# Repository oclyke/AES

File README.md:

# AES

This repo contains folders for both hardware and software. 

Hardware is designed in Eagle.

Software uses the HAL library for STM32F4 and I reccomend the Atollic TRUEStudio development environment. STM32Cube is a great tool for generating skeleton code and configuring peripherals.

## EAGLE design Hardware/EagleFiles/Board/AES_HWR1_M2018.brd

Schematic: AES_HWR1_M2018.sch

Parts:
C1, C7, C18, C25, C26, C27, C29, C30, C32, C36, C38, C39, C40, C41, C42, C43, C44: 0.1uF; 0603
C2, C19: 10uF; 1206
C3, C10, C11, C12, C13: 560pF; 0603
C4: 220uF; 2917_P
C5: 22uF; 1206
C6, C8, C14, C15, C20, C28, C31, C33, C45: 1uF; 0603
C16: 150pF; 0603
C17: 4.7uF, 25V; 0603
C21, C22: 30pF; 0603
C23, C24: 10uF; 0603
C34, C35: 10pF; 0603
C37: 4.7uF; 0603
D1: 18V, 5W; DO-214AA
D2: 3V3; 0603-POLAR
D3, D7: PASS_DIODE_SCHOTTKY-LSM115J; DO-214BA
D4: OBD_STAT; 0603-POLAR
D5: OBD_ACT; 0603-POLAR
D6: OBD_HOST_ACT; 0603-POLAR
D8, D9: PASS_DIODE_ESD_CAN-PESD1CAN-UX; SOT23-3
D10, D11, D12, D13, D20, D21: PASS_DIODE_GEN-1N4148X; SOD-523
D14: BLU_CONN; 0603-POLAR
D15: TXRX_ACT; 0603-POLAR
D16: 5V; 0603-POLAR
D18: UL1; 0603-POLAR
D19: UL2; 0603-POLAR
F2: PASS_FUSE_POLY-1206L200SLYR; 1206
F3: 500mA; 1206
J1: BFR; 1X02
J2: BSB; 1X02
J3: BSM; 1X02
J4: BAD; 1X02
J5: BOOT1; 1X03
J6: SWD; 1X04
J7: RESET_NVM_L; SMD_HEADER_0.1IN_2POS
J8: BOOT0; 1X02
M1: SD CARD; SD_AMPHENOL_PUSH_PULL
M2: USB_MICRO-MID_MOUNT_REVERSIBLE; MICROUSB
M3: ALED0; 3_PIN_LOCK
M4: ALED1; 3_PIN_LOCK
M5: ALED2; 3_PIN_LOCK
M6: ALED3; 3_PIN_LOCK
M7: I2C_EXP; 4_PIN_LOCK
M8: UART EXP; 4_PIN_LOCK
M9: AUX PWR; 2_PIN_LOCK
M10: OBD_CONN-4-794627-6; OBD_16_SMD
M11: SIG_IN; 4_PIN_LOCK
M12: EXT_PWR_SW; 3_PIN_LOCK
Q1, Q2, Q3, Q4, Q9, Q10, Q11: PASS_NMOS-2N7002K; SOT23-3@1
Q5, Q7, Q12, Q17: AMP_MOSFET_PCH-MCQ4459; SOP-8
Q6, Q15, Q16, Q18, Q19, Q20, Q21, Q22, Q23, Q24, Q25, Q26, Q27: AMP_MOSFET_NCH-2N7002K; SOT23-3
Q8: PASS_PMOS-MCQ4459; SOP-8@1
Q13, Q14: AMP_BJT_NPNZXTN19100CFF; SOT23-3
R1, R2, R3, R4, R5, R6, R7, R8, R11, R13, R19, R37, R38, R39, R40, R44, R45, R46, R47, R49, R50, R51, R52, R53, R54, R55, R66, R67, R70, R71, R72, R73, R74, R75, R76, R77, R78, R79, R80, R81, R82, R83, R84, R85, R86, R87, R88, R89, R90, R91, R94, R101, R102, R104: 10k; 0603
R9: TRMD; 0603
R10: TRMU; 0603
R12, R92: 22; 0603
R14, R105: 300; 0603
R15, R16: PASS_RES-SMD_0603; 0603
R17: 10; 0603
R18: 62k; 0603
R20, R21, R22, R68, R69, R95, R96: 330; 0603
R23, R24, R59, R60, R61, R62, R63, R64: 100k; 0603
R25, R26, R99, R100: 4k7; 0603
R27, R28, R29, R30: 100; 0603
R31, R35, R36, R56, R58: 1k; 0603
R32: 6k49; 0603
R33, R34: 510 1/2W; 1206
R41: 240; 0603
R42: 866; 0603
R43: 374; 0603
R48: 2k7; 0603
R57, R65: 1k5; 0603
R93: 1M; 0603
R97, R98: 2k2; 0603
R103: 130 2W; 2512
S1: RESET; PTS525
S2: US2; PTS525
S3: US1; PTS525
S4: SWITCH_SPDT_SLIDE_SPARKFUN_SMD; SPARKFUNSWITCH
TP1: GPIO2; PAD.03X.05
TP2: REV3V3; PAD.03X.05
TP3: RTS3V3; PAD.03X.05
TP4: LTS3V3; PAD.03X.05
TP5: BRK3V3; PAD.03X.05
TP6: REV12V; PAD.03X.05
TP7: RTS12V; PAD.03X.05
TP8: LTS12V; PAD.03X.05
TP9: BRK12V; PAD.03X.05
TP10, TP71: VRAW; PAD.03X.05
TP11: VREVP; PAD.03X.05
TP12: VBATT; PAD.03X.05
TP13: 5V; PAD.03X.05
TP14: 3V3; PAD.03X.05
TP15, TP35, TP44, TP53, TP54, TP78, TP110, TP111, TP112, TP113: GND; PAD.03X.05
TP16: S2CK3V3; PAD.03X.05
TP17: S2CK5V; PAD.03X.05
TP18: S2MO3V3; PAD.03X.05
TP19: S2MO5V; PAD.03X.05
TP20: S3CK3V3; PAD.03X.05
TP21: S3CK5V; PAD.03X.05
TP22: S3MO3V3; PAD.03X.05
TP23: S3MO5V; PAD.03X.05
TP24: S4CK3V3; PAD.03X.05
TP25: S4CK5V; PAD.03X.05
TP26: S4MO3V3; PAD.03X.05
TP27: S4MO5V; PAD.03X.05
TP28: S5CK3V3; PAD.03X.05
TP29: S5CK5V; PAD.03X.05
TP30: S5MO3V3; PAD.03X.05
TP31: S5MO5V; PAD.03X.05
TP32: S1MISO; PAD.03X.05
TP33: S1MOSI; PAD.03X.05
TP34: S1CLK; PAD.03X.05
TP36: CSMAG; PAD.03X.05
TP37: CSACC; PAD.03X.05
TP38: CSGYRO; PAD.03X.05
TP39: U2RX; PAD.03X.05
TP40: U2TX; PAD.03X.05
TP41: U2CTS; PAD.03X.05
TP42: U1RX; PAD.03X.05
TP43: U1TX; PAD.03X.05
TP45: U6RX; PAD.03X.05
TP46: U6TX; PAD.03X.05
TP47: I2C1DA; PAD.03X.05
TP48: I2C1CL; PAD.03X.05
TP49: BFR; PAD.03X.05
TP50: BSBR; PAD.03X.05
TP51: BSBM; PAD.03X.05
TP52: BAD; PAD.03X.05
TP55: SWCLK; PAD.03X.05
TP56: SWDIO; PAD.03X.05
TP57: RESETL; PAD.03X.05
TP58: BOOT0; PAD.03X.05
TP59: UD1L; PAD.03X.05
TP60: UD2L; PAD.03X.05
TP61: USBDP; PAD.03X.05
TP62: USBDM; PAD.03X.05
TP63: SDD0; PAD.03X.05
TP64: SDD1; PAD.03X.05
TP65: SDD2; PAD.03X.05
TP66: SDD3; PAD.03X.05
TP67: SDCK; PAD.03X.05
TP68: SDCMD; PAD.03X.05
TP70: CMPO; PAD.03X.05
TP72: L; PAD.03X.05
TP73: HSCL; PAD.03X.05
TP74: MSCL; PAD.03X.05
TP75: J-; PAD.03X.05
TP76: K; PAD.03X.05
TP77: HSCH; PAD.03X.05
TP79: KTX; PAD.03X.05
TP80: MSCH; PAD.03X.05
TP81: J+; PAD.03X.05
TP82: SWC; PAD.03X.05
TP83: LTX; PAD.03X.05
TP84: VBISO; PAD.03X.05
TP85: ISORL; PAD.03X.05
TP86: HSCT; PAD.03X.05
TP87: HSCR; PAD.03X.05
TP88: SWCT; PAD.03X.05
TP89: SWCR; PAD.03X.05
TP90: MSCT; PAD.03X.05
TP91: MSCR; PAD.03X.05
TP92: SWCM0; PAD.03X.05
TP93: SWCM1; PAD.03X.05
TP94: VBSW; PAD.03X.05
TP95: 5VSW; PAD.03X.05
TP96: 3V3SW; PAD.03X.05
TP97: PSL; PAD.03X.05
TP98: OSD; PAD.03X.05
TP99: HAD; PAD.03X.05
TP100: OAD; PAD.03X.05
TP101: OAI; PAD.03X.05
TP102: J-TL; PAD.03X.05
TP103: J+T; PAD.03X.05
TP104: VJ; PAD.03X.05
TP105: VPWR; PAD.03X.05
TP106: PWMR; PAD.03X.05
TP107: J+VHL; PAD.03X.05
TP108: DCDC5; PAD.03X.05
TP109: USB5; PAD.03X.05
U1: IC_VREF_3PIN-NCP51460SN33T1G; SOT23-3
U2, U12, U14: IC_OP-AMP_DUAL-OPA1662AIDR; SOIC-8
U3: DCDC_5V; CUI-5
U6: 3.3VREG_USB_POWER; SOT23-5
U7: STN2120; QFN-44
U9, U10: IC_OBD_TXRX_CAN_MCP2551; SOIC-8@1
U11: IC_OBD_TXRX_SWCAN-TH8056A; SOIC-8
U13: REG_LINEAR_3LM317LD; SOIC-8
U15: ACC; LGA-16
U16: GYRO; QFN-24
U17: MAG; VFLGA-12
U18: Bluetooth UART; RN42
U19: STM32F411; LQFP-64
X1: XTAL-FA238; FA-238
X2: 16MHz; FA-238

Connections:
3.3V: C8.1, C20.2, C23.1, C24.1, C25.2, C26.2, C28.1, C29.1, C30.1, C31.2, C32.2, C33.2, C36.1, C38.1, C39.1, C40.1, C41.1, C42.1, C43.1, D2.+ (A), D5.+ (A), D6.+ (A), D14.+ (A), D15.+ (A), D18.+ (A), D19.+ (A), D21.C, J1.2, J2.2, J3.2, J5.1, J6.4, J8.2, M1.P$4 (VDD), M7.P$3 (3), M8.P$3 (3), Q1.1 (G), Q2.1 (G), Q3.1 (G), Q4.1 (G), Q11.3 (D), Q19.1 (G), Q20.1 (G), Q21.1 (G), Q22.1 (G), Q23.1 (G), Q24.1 (G), Q25.1 (G), Q26.1 (G), R1.2, R3.2, R5.2, R7.2, R13.2, R17.1, R23.2, R31.2, R40.2, R46.2, R50.2, R58.2, R59.2, R60.2, R61.2, R62.2, R63.1, R64.2, R73.1, R74.2, R76.2, R78.2, R80.2, R82.2, R84.2, R86.2, R88.2, R94.1, R97.2, R98.2, R99.1, R100.1, S2.P$3 (2), S2.P$4 (2), S3.P$3 (2), S3.P$4 (2), TP14.P$1, U6.5 (VOUT), U7.P$28 (28.VDD_0), U7.P$40 (40.VDD_1), U15.P$1 (1.VDD_IO), U15.P$14 (14.VDD), U16.P$4 (4.RST_B), U16.P$8 (8.I2C_B/SPI), U16.P$15 (15.VDD), U16.P$18 (18.VDDIO), U17.P$5 (VDD), U17.P$6 (VDD_IO), U18.P$11 (11.VDD), U19.P$13 (VDDA/VREF+), U19.P$19 (VDD), U19.P$32 (VDD_1), U19.P$48 (VDD_2), U19.P$64 (VDD_3)
3V3_SW: Q11.2 (S), TP96.P$1
5V: D3.C, D7.C, D16.+ (A), Q10.3 (D), R65.2, R75.2, R77.2, R79.2, R81.2, R83.2, R85.2, R87.2, R89.2, TP13.P$1, U6.1 (VIN), U6.3 (INHIBIT)
5V_SW: C14.1, C15.1, D13.A, Q10.2 (S), R48.2, R54.2, R56.2, R57.2, R66.2, R67.2, TP95.P$1, U9.3 (VDD), U10.3 (VDD)
5V_USB: D7.A, F3.1, TP109.P$1
BLU_AUTO_DISC: J4.1, R73.2, TP52.P$1, U18.P$20 (20.GPIO3)
BLU_CONN_STAT_LED: R68.1, U18.P$21 (21.GPIO5)
BLU_FACT_RESET: J1.1, R70.2, TP49.P$1, U18.P$22 (22.GPIO4)
BLU_SET_BR: J2.1, R71.2, TP50.P$1, U18.P$4 (4.GPIO7)
BLU_SET_BT_MAST: J3.1, R72.2, TP51.P$1, U18.P$3 (3.GPIO6)
BLU_SPI_CS: U18.P$23 (23.SPI_CSB)
BLU_SPI_MISO: U18.P$24 (24.SPI_MISO)
BLU_SPI_MOSI: U18.P$2 (2.SPI_MOSI)
BLU_SPI_SCLK: U18.P$6 (6.SPI_CLOCK)
BLU_TXRX_ACT_LED: R69.1, U18.P$31 (31.GPIO8)
BOOT0: J8.1, R90.2, TP58.P$1, U19.P$60 (BOOT0)
BRK_3V3: Q1.2 (S), R1.1, TP5.P$1, U19.P$51 (PC10)
BRK_12V: M11.P$1 (1), Q1.3 (D), R2.1, TP9.P$1
COMP_OUT: Q6.1 (G), TP70.P$1, U2.1 (OUTA)
DCDC5V: C4.PIN_2_+ (+), C5.1, D3.A, R9.2, TP108.P$1, U3.5 (VOUT)
GND: C1.2, C2.2, C3.2, C4.PIN_1_- (-), C5.2, C6.2, C7.1, C8.2, C10.1, C11.1, C12.1, C13.1, C14.2, C15.2, C16.1, C17.2, C18.1, C19.1, C20.1, C21.1, C22.2, C23.2, C24.2, C25.1, C26.1, C27.1, C28.2, C29.2, C31.1, C32.1, C33.1, C34.1, C35.1, C36.2, C37.2, C38.2, C39.2, C40.2, C41.2, C42.2, C43.2, C44.2, C45.1, D1.A, D4.- (C), D8.3 (C), D9.3 (C), D10.A, D12.C, D20.A, J4.2, J5.3, J6.3, J7.P$1 (1), M1.CD_SW1, M1.P$6 (VSS1), M2.5 (GND), M3.P$2 (2), M4.P$2 (2), M5.P$2 (2), M6.P$2 (2), M7.P$4 (4), M8.P$4 (4), M9.P$2 (1), M10.4 (4.GND_CHASSIS), M10.5 (5.GND_SIGNAL), Q5.5 (G), Q6.2 (S), Q8.5 (D), Q8.6 (D), Q8.7 (D), Q8.8 (D), Q13.2 (E), Q14.2 (E), Q15.2 (S), Q16.2 (S), Q18.2 (S), Q27.2 (S), R10.1, R14.1, R16.1, R19.1, R25.1, R26.1, R38.1, R43.1, R49.1, R52.1, R70.1, R71.1, R72.1, R90.1, R93.2, R101.1, R102.1, R104.1, R105.1, S1.P$1 (1), S1.P$2 (1), S4.COM, TP15.P$1, TP35.P$1, TP44.P$1, TP53.P$1, TP54.P$1, TP78.P$1, TP110.P$1, TP111.P$1, TP112.P$1, TP113.P$1, U1.3 (GND), U2.4 (V-), U3.7 (GND), U3.9 (GND), U6.2 (GND), U7.P$1 (1.GP28), U7.P$2 (2.GP29), U7.P$3 (3.GP30), U7.P$6 (6.VSS), U7.P$15 (15.GP31), U7.P$16 (16.AVSS), U7.P$20 (20.GP32), U7.P$26 (26.GP33), U7.P$29 (29.VSS_0), U7.P$37 (37.GP34), U7.P$38 (38.GP35), U7.P$39 (39.VSS_1), U7.P$45 (PAD), U9.2 (VSS), U10.2 (VSS), U11.8 (GND), U12.4 (V-), U14.4 (V-), U15.P$5 (5.GND), U15.P$10 (10.RES), U15.P$12 (12.GND), U15.P$13 (13.ADC3), U15.P$15 (15.ADC2), U15.P$16 (16.ADC1), U16.P$1 (1.GND1), U16.P$5 (5.GND2), U16.P$6 (6.RSVD_GND1), U16.P$7 (7.RSVD_GND2), U16.P$9 (9.RSVD_GND3), U16.P$10 (10.RSVD_GND4), U16.P$14 (14.GND3), U16.P$19 (19.GND4), U16.P$20 (20.RSVD_GND5), U16.P$21 (21.RSVD_GND6), U16.P$22 (22.RSVD_GND7), U16.P$23 (23.RSVD_GND8), U16.P$24 (24.RSVD_GND9), U17.P$2 (RES), U17.P$3 (GND), U17.P$12 (RES_1), U18.P$1 (1.GND), U18.P$12 (12.GND1), U18.P$28 (28.GND3), U18.P$29 (29.GND2), U18.SHEILD1 (SHIELD), U18.SHEILD2 (SHIELD), U18.SHEILD3 (SHIELD), U18.SHEILD4 (SHIELD), U19.P$12 (VSSA/VREF-), U19.P$18 (VSS), U19.P$31 (VSS_1), U19.P$47 (VSS_2), U19.P$63 (VSS_3), X1.P$2 (COVER), X1.P$4 (COVER), X2.P$2 (COVER), X2.P$4 (COVER)
HS_CAN_HI: D8.2 (C1), M10.6 (6.HS_CAN_HI), R27.2, TP77.P$1, U9.7 (CANH)
HS_CAN_LO: D8.1 (C2), M10.14 (14.HS_CAN_LO), R28.2, TP73.P$1, U9.8 (CANL)
HS_CAN_RX: R57.1, R61.1, TP87.P$1, U7.P$10 (10.HS_CAN_RX/GP8), U9.4 (ROUT)
HS_CAN_TX: R56.1, R59.1, TP86.P$1, U7.P$8 (8.HS_CAN_TX/GP9), U9.1 (TIN)
I2C1_SCL: M7.P$1 (1), R100.2, TP48.P$1, U19.P$58 (PB6)
I2C1_SDA: M7.P$2 (2), R99.2, TP47.P$1, U19.P$59 (PB7)
ISO_K_TX_L: R35.1, TP79.P$1, U7.P$43 (43.ISO_K_TX_L/GP6)
ISO_L_TX_L: R36.1, TP83.P$1, U7.P$44 (44.ISO_L_TX_L/GP7)
ISO_RX_L: R40.1, TP85.P$1, U7.P$21 (21.ISO_RX_L/GP5), U12.1 (OUTA)
J1850_BUS+: D11.C, M10.2 (2.J1850_PWM/VPW_POS), R44.1, R47.2, R53.1, TP81.P$1
J1850_BUS+_TX: Q16.1 (G), R52.2, TP103.P$1, U7.P$24 (24.J1850_BUS+_TX/GP2)
J1850_BUS+_VH_L: Q15.1 (G), TP107.P$1, U7.P$25 (25.J1850_BUS+_VH_L/GP4)
J1850_BUS-: M10.10 (10.J1850_PWM_NEG), Q18.3 (D), R45.1, R55.1, TP75.P$1
J1850_BUS-_TX_L: Q18.1 (G), R54.1, TP102.P$1, U7.P$33 (33.J1850_BUS-_TX_L/GP3)
K_LINE: M10.7 (7.KLINE), Q13.3 (C), R33.1, R39.1, TP76.P$1
LTS_3V3: Q2.2 (S), R3.1, TP4.P$1, U19.P$56 (PB4)
LTS_12V: M11.P$2 (2), Q2.3 (D), R4.1, TP8.P$1
L_LINE: M10.15 (15.LLINE), Q14.3 (C), R34.1, TP72.P$1
MS_CAN_HI: D9.2 (C1), M10.3 (3.MS_CAN_HI), R29.2, TP80.P$1, U10.7 (CANH)
MS_CAN_LO: D9.1 (C2), M10.11 (11.MS_CAN_LO), R30.2, TP74.P$1, U10.8 (CANL)
MS_CAN_RX: R62.1, TP91.P$1, U7.P$11 (11.MS_CAN_RX/GP10), U10.4 (ROUT)
MS_CAN_TX: R60.1, TP90.P$1, U7.P$9 (9.MS_CAN_TX/GP11), U10.1 (TIN)
unnamed: M12.P$3 (3), Q7.5 (G), R91.1, S4.C2
unnamed: C3.1, R9.1, R10.2, U3.6 (VADJ)
unnamed: Q6.3 (D), R11.1, U3.10 (ON/OFF_L)
unnamed: M12.P$1 (1), S4.C1
unnamed: C6.1, R17.2, U7.P$17 (17.AVDD)
unnamed: J6.1, R12.2
unnamed: D5.- (C), R21.2
unnamed: D4.+ (A), R20.1
unnamed: D6.- (C), R22.2
unnamed: C13.2, R28.1
unnamed: C12.2, R27.1
unnamed: R25.2, U10.6 (RS)
unnamed: C10.2, R29.1
unnamed: R26.2, U9.6 (RS)
unnamed: F3.2, M2.1 (VBUS)
unnamed: Q8.1 (S), Q8.2 (S), Q8.3 (S), Q9.1 (G), Q10.1 (G), Q11.1 (G), R24.1
unnamed: C11.2, R30.1
unnamed: R37.1, R38.2, U12.3 (+INA)
unnamed: R32.1, U11.6 (LOAD)
unnamed: R39.2, U12.2 (-INA)
unnamed: Q13.1 (B), R35.2
unnamed: R44.2, U14.3 (+INA)
unnamed: Q14.1 (B), R36.2
unnamed: R45.2, U14.2 (-INA)
unnamed: Q15.3 (D), R42.1, R43.2
unnamed: R41.1, R42.2, U13.4 (ADJ)
unnamed: C19.2, U7.P$7 (7.VCAP)
unnamed: D10.C, R47.1, U14.5 (+INB)
unnamed: D11.A, Q17.1 (D), Q17.2 (D), Q17.3 (D), Q17.4 (D)
unnamed: R48.1, R49.2, U14.6 (-INB)
unnamed: Q16.3 (D), Q17.5 (G), R51.1
unnamed: D13.C, R55.2
unnamed: D12.A, R53.2
unnamed: C30.2, U17.P$4 (C1)
unnamed: D14.- (C), R68.2
unnamed: D15.- (C), R69.2
unnamed: C21.2, U7.P$30 (30.OSC1), X1.P$1 (1)
unnamed: C22.1, U7.P$31 (31.OSC2), X1.P$3 (2)
unnamed: C27.2, U16.P$16 (16.VREGD)
unnamed: C35.2, U19.P$6 (PH1-OSC_OUT), X2.P$3 (2)
unnamed: TP1.P$1, U18.P$19 (19.GPIO2)
unnamed: C34.2, U19.P$5 (PH0-OSC_IN), X2.P$1 (1)
unnamed: D2.- (C), R14.2
unnamed: J6.2, R92.2
unnamed: D18.- (C), R95.2
unnamed: Q27.3 (D), R103.P$1 (1)
unnamed: D19.- (C), R96.2
unnamed: Q5.6 (S), Q5.7 (S), Q5.8 (S), Q7.6 (S), Q7.7 (S), Q7.8 (S), R91.2
unnamed: C45.2, M2.MOUNT5T (SHIELD), R93.1
unnamed: D16.- (C), R105.2
unnamed: C37.1, U19.P$30 (VCAP_1)
OBD_ANALOG_IN: C7.2, D20.C, D21.A, R18.1, R19.2, TP101.P$1, U7.P$19 (19.ANALOG_IN/GP17)
OBD_HOST_ACT_LED: R22.1, TP99.P$1, U7.P$13 (13.LED_HOST_ACT_L/GP24)
OBD_OBD_ACT_LED: J7.P$2 (2), R21.1, R63.2, TP100.P$1, U7.P$12 (12.LED_OBD_ACT_L/RST_NVM_L/GP22)
OBD_STATUS_LED: R20.2, TP98.P$1, U7.P$14 (14.LED_STATUS/GP26)
PWM_RX: R46.1, TP106.P$1, U7.P$23 (23.PWM_RX/GP0), U14.1 (OUTA)
PWR_SAVE_L: Q8.4 (G), Q12.5 (G), R23.1, TP97.P$1, U7.P$32 (32.PWR_CTRL/GP19)
RESET_L: C44.1, R13.1, S1.P$3 (2), S1.P$4 (2), TP57.P$1, U7.P$18 (18.RESET_L), U18.P$5 (5.RESET), U19.P$7 (NRST)
REV_3V3: Q4.2 (S), R7.1, TP2.P$1, U19.P$62 (PB9)
REV_12V: M11.P$4 (4), Q4.3 (D), R8.1, TP6.P$1
RTS_3V3: Q3.2 (S), R5.1, TP3.P$1, U19.P$57 (PB5)
RTS_12V: M11.P$3 (3), Q3.3 (D), R6.1, TP7.P$1
SDIO_CK: M1.P$5 (CLK), TP67.P$1, U19.P$36 (PB15)
SDIO_CMD: M1.P$3 (CMD), TP68.P$1, U19.P$54 (PD2)
SDIO_D0: M1.P$7 (DAT0), TP63.P$1, U19.P$39 (PC8)
SDIO_D1: M1.P$8 (DAT1), TP64.P$1, U19.P$40 (PC9)
SDIO_D2: M1.P$1 (DAT2), TP65.P$1, U19.P$42 (PA9)
SDIO_D3: M1.P$2 (CD/DAT3), TP66.P$1, U19.P$52 (PC11)
SD_CD_L: M1.CD_SW2, R94.2, U19.P$10 (PC2)
SLEEP_L: R64.1, U7.P$27 (27.SLEEP_L/GP18)
SPI1_CS_ACC: TP37.P$1, U15.P$8 (8.CS), U19.P$35 (PB14)
SPI1_CS_GYRO: TP38.P$1, U16.P$17 (17.SPI_CS_B), U19.P$27 (PB1)
SPI1_CS_MAG: J5.2, TP36.P$1, U17.P$10 (CS), U19.P$28 (PB2)
SPI1_MISO: TP32.P$1, U15.P$7 (7.SDO/SA0), U16.P$13 (13.SA0/MISO), U17.P$9 (SD0/SA1), U19.P$22 (PA6)
SPI1_MOSI: TP33.P$1, U15.P$6 (6.SDA/SDI/SDO), U16.P$12 (12.SDA/MOSI/SPI_DATA), U17.P$11 (SDA/SDI/SDO), U19.P$23 (PA7)
SPI1_SCK: TP34.P$1, U15.P$4 (4.SCL/SPC), U16.P$11 (11.SCL/SCLK), U17.P$1 (SCL/SPC), U19.P$21 (PA5)
SPI2_MOSI_3V3: Q20.2 (S), R76.1, TP18.P$1, U19.P$11 (PC3)
SPI2_MOSI_5V: M3.P$1 (1), Q20.3 (D), R77.1, TP19.P$1
SPI2_SCK_3V3: Q19.2 (S), R74.1, TP16.P$1, U19.P$29 (PB10)
SPI2_SCK_5V: M3.P$3 (3), Q19.3 (D), R75.1, TP17.P$1
SPI3_MOSI_3V3: Q22.2 (S), R80.1, TP22.P$1, U19.P$53 (PC12)
SPI3_MOSI_5V: M4.P$1 (1), Q22.3 (D), R81.1, TP23.P$1
SPI3_SCK_3V3: Q21.2 (S), R78.1, TP20.P$1, U19.P$33 (PB12)
SPI3_SCK_5V: M4.P$3 (3), Q21.3 (D), R79.1, TP21.P$1
SPI4_MOSI_3V3: Q24.2 (S), R84.1, TP26.P$1, U19.P$15 (PA1)
SPI4_MOSI_5V: M5.P$1 (1), Q24.3 (D), R85.1, TP27.P$1
SPI4_SCK_3V3: Q23.2 (S), R82.1, TP24.P$1, U19.P$34 (PB13)
SPI4_SCK_5V: M5.P$3 (3), Q23.3 (D), R83.1, TP25.P$1
SPI5_MOSI_3V3: Q26.2 (S), R88.1, TP30.P$1, U19.P$61 (PB8)
SPI5_MOSI_5V: M6.P$1 (1), Q26.3 (D), R89.1, TP31.P$1
SPI5_SCK_3V3: Q25.2 (S), R86.1, TP28.P$1, U19.P$26 (PB0)
SPI5_SCK_5V: M6.P$3 (3), Q25.3 (D), R87.1, TP29.P$1
SWCLK: R12.1, R97.1, TP55.P$1, U19.P$49 (PA14)
SWDIO: R92.1, R98.1, TP56.P$1, U19.P$46 (PA13)
SW_CAN: C16.2, M10.1 (1.SWCAN), R32.2, R103.P$2 (2), TP82.P$1, U11.7 (CANH)
SW_CAN_LOAD: Q27.1 (G), R104.2, U7.P$34 (34.SW_CAN_LOAD/GP16)
SW_CAN_MODE0: R67.1, TP92.P$1, U7.P$35 (35.SW_CAN_MODE0/GP14), U11.2 (MODE0)
SW_CAN_MODE1: R66.1, TP93.P$1, U7.P$36 (36.SW_CAN_MODE1/GP15), U11.3 (MODE1)
SW_CAN_RX: R31.1, TP89.P$1, U7.P$42 (42.SW_CAN_RX/GP12), U11.4 (ROUT)
SW_CAN_TX: R65.1, TP88.P$1, U7.P$41 (41.SW_CAN_TX/GP13), U11.1 (TIN)
US1: R102.2, S3.P$1 (1), S3.P$2 (1), U19.P$20 (PA4)
US2: R101.2, S2.P$1 (1), S2.P$2 (1), U19.P$24 (PC4)
USART1_RX: R58.1, TP42.P$1, U7.P$4 (4.UART_TX), U19.P$55 (PB3)
USART1_TX: TP43.P$1, U7.P$5 (5.UART_RX), U19.P$50 (PA15)
USART2_CTS: TP41.P$1, U18.P$15 (15.UART_RTS), U19.P$14 (PA0)
USART2_RX: TP39.P$1, U18.P$13 (13.UART_RX), U19.P$17 (PA3)
USART2_TX: TP40.P$1, U18.P$14 (14.UART_TX), U19.P$16 (PA2)
USART6_RX: M8.P$1 (1), TP45.P$1, U19.P$38 (PC7)
USART6_TX: M8.P$2 (2), TP46.P$1, U19.P$37 (PC6)
USB_OTG_FS_DM: M2.2 (D-), TP62.P$1, U19.P$44 (PA11)
USB_OTG_FS_DP: M2.3 (D+), TP61.P$1, U19.P$45 (PA12)
USER_LED1L: R95.1, TP59.P$1, U19.P$8 (PC0)
USER_LED2L: R96.1, TP60.P$1, U19.P$9 (PC1)
VPW_RX: R50.1, TP105.P$1, U7.P$22 (22.VPW_RX/GP1), U14.7 (OUTB)
V_BACKUP: U19.P$1 (VBAT)
V_BATT: C2.1, C17.1, D1.C, F2.2, Q9.3 (D), Q12.6 (S), Q12.7 (S), Q12.8 (S), R2.2, R4.2, R6.2, R8.2, R11.2, R15.2, R18.2, R24.2, TP12.P$1, U1.1 (VIN), U2.8 (V+), U3.1 (VIN), U11.5 (VBAT), U12.8 (V+)
V_BATT_ISO: Q12.1 (D), Q12.2 (D), Q12.3 (D), Q12.4 (D), R33.2, R34.2, TP84.P$1
V_BATT_RAW: M9.P$3 (2), M10.16 (16.+12V_ALWAYS_ON), Q5.1 (D), Q5.2 (D), Q5.3 (D), Q5.4 (D), TP10.P$1, TP71.P$1
V_BATT_REVP: C1.1, F2.1, Q7.1 (D), Q7.2 (D), Q7.3 (D), Q7.4 (D), TP11.P$1
V_BATT_SW: C18.2, Q9.2 (S), R37.2, TP94.P$1, U13.1 (VIN), U14.8 (V+)
V_COMP_+: U1.2 (VOUT), U2.3 (+INA)
V_COMP_-: R15.1, R16.2, U2.2 (-INA)
V_J1850: Q17.6 (S), Q17.7 (S), Q17.8 (S), R41.2, R51.2, TP104.P$1, U13.2 (VOUT), U13.3 (VOUT), U13.6 (VOUT), U13.7 (VOUT)

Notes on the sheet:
Signal Input Protection
LED Output Conditioning
Battery Sense Circuit
Status LEDs
OBD-II Connector
Power Saving Switches
Optional ESD Pro.
HS / MS CAN Transceiver
SW CAN Transceiver
ISO Transceiver
How TF does this work? Seems like the gate will always be too low to turn the switch off...
J1850 Transceiver
Note: RESET_L already has a 10k pulllup to 3V3 in the power supply block
STN2120
External Sensors
Bluetooth UART Module
Micro + Related
BOOT0 Jumper
RESET + PULLUP
SWD
USER LEDS
VBATT + Capacitance
Seeed GROVE I2C EXP
Seeed GROVE USART EXP
Input Signals
Power
LED Output Lines
Sensor SPI Lines
General Serial Interfaces
Bluetooth Options
SD, USB, SWD, LEDS, RESET
RAW OBD Inputs
CAN
Switched Supplies
SWCAN
Status + Pwr Save
OBD Test Points
Test Points
User Buttons
Regulator and VBATT Comparator

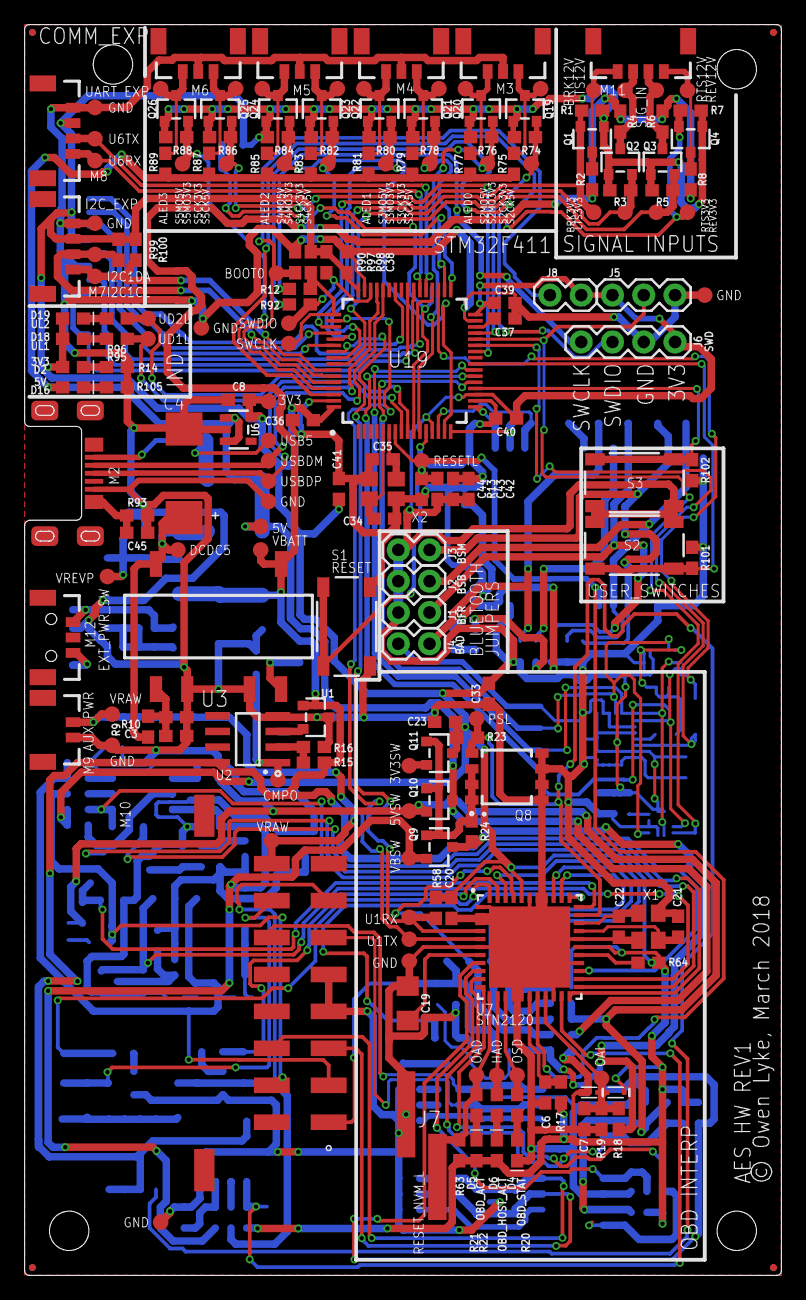
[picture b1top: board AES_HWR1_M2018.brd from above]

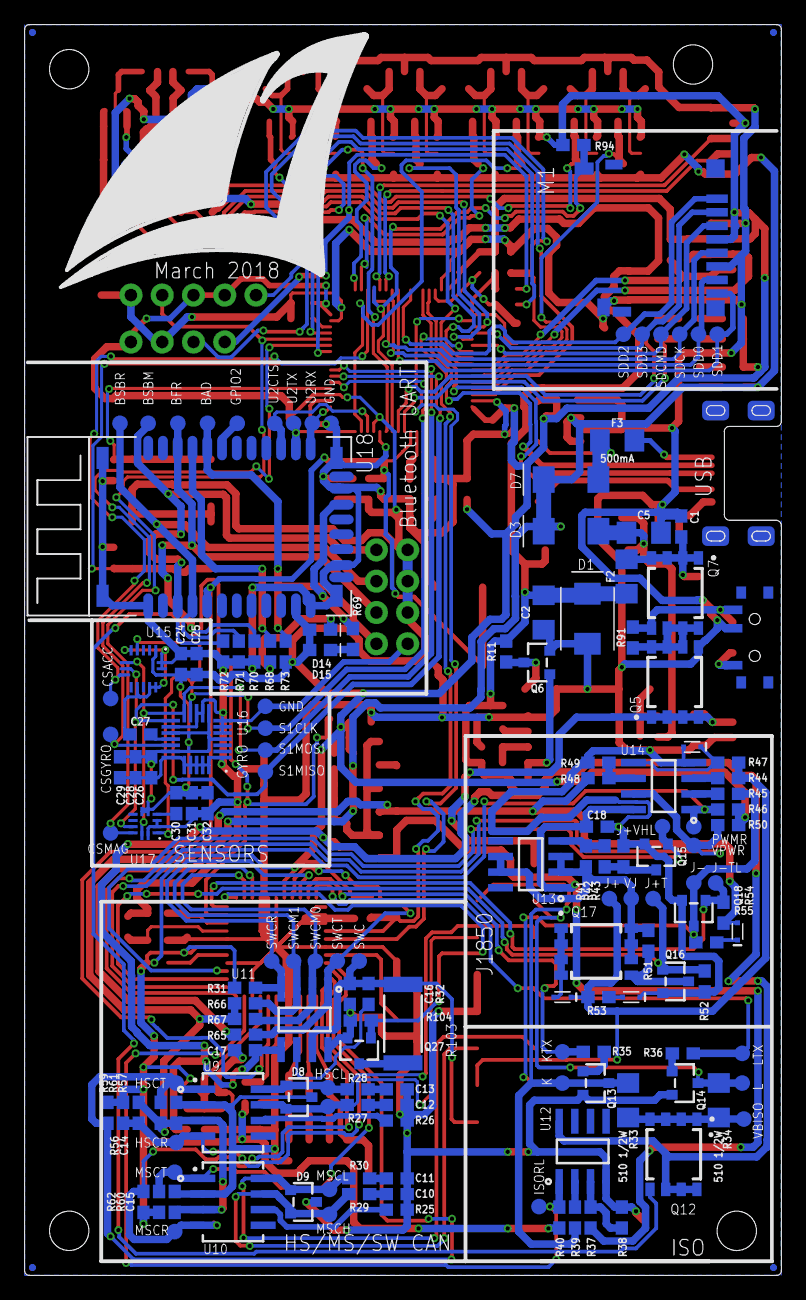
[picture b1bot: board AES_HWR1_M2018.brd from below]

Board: 2 copper layers, 61.5 x 101.6 mm, 352 parts (157 on the bottom side), 161 nets.

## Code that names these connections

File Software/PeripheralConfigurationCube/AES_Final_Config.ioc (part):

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Mcu.Name=STM32F411R(C-E)Tx
Mcu.Package=LQFP64
Mcu.UserName=STM32F411RETx
PA0-WKUP.Mode=CTS_Only
PA0-WKUP.Signal=USART2_CTS
PA1.Mode=TX_Only_Simplex_Unidirect_Master
PA1.Signal=SPI4_MOSI
PA10.GPIOParameters=GPIO_Label
PA10.GPIO_Label=SD_CD
PA10.Signal=GPIO_Input
PA11.Mode=Device_Only
PA11.Signal=USB_OTG_FS_DM
PA12.Mode=Device_Only
PA12.Signal=USB_OTG_FS_DP
PA13.Signal=SYS_JTMS-SWDIO
PA14.Signal=SYS_JTCK-SWCLK
PA15.Mode=Asynchronous
PA15.Signal=USART1_TX
PA2.Mode=Asynchronous
PA2.Signal=USART2_TX
PA3.Mode=Asynchronous
PA3.Signal=USART2_RX
PA4.GPIOParameters=GPIO_PuPd,GPIO_Label
PA4.GPIO_Label=US1
PA4.GPIO_PuPd=GPIO_NOPULL
PA4.Signal=GPIO_Input
PA5.Mode=Full_Duplex_Master
PA5.Signal=SPI1_SCK
PA6.Mode=Full_Duplex_Master
PA6.Signal=SPI1_MISO
PA7.Mode=Full_Duplex_Master
PA7.Signal=SPI1_MOSI
PA9.Mode=SD_4_bits_Wide_bus
PA9.Signal=SDIO_D2
PB0.Mode=TX_Only_Simplex_Unidirect_Master
PB0.Signal=SPI5_SCK
PB1.GPIOParameters=PinState,GPIO_PuPd,GPIO_Label
PB1.GPIO_Label=CS_GYRO
PB1.GPIO_PuPd=GPIO_PULLUP
PB1.PinState=GPIO_PIN_SET
PB1.Signal=GPIO_Output
PB10.Mode=TX_Only_Simplex_Unidirect_Master
PB10.Signal=SPI2_SCK
PB12.Mode=TX_Only_Simplex_Unidirect_Master
PB12.Signal=SPI3_SCK
PB13.Mode=TX_Only_Simplex_Unidirect_Master
PB13.Signal=SPI4_SCK
PB14.GPIOParameters=PinState,GPIO_PuPd,GPIO_Label
PB14.GPIO_Label=CS_ACC
PB14.GPIO_PuPd=GPIO_PULLUP
PB14.PinState=GPIO_PIN_SET
PB14.Signal=GPIO_Output
PB15.Mode=SD_4_bits_Wide_bus
PB15.Signal=SDIO_CK
PB2.GPIOParameters=GPIO_Speed,PinState,GPIO_PuPd,GPIO_Label
PB2.GPIO_Label=CS_MAG
PB2.GPIO_PuPd=GPIO_PULLUP
PB2.GPIO_Speed=GPIO_SPEED_FREQ_LOW
PB2.PinState=GPIO_PIN_SET
PB2.Signal=GPIO_Output
PB3.Mode=Asynchronous
PB3.Signal=USART1_RX
PB4.GPIOParameters=GPIO_Label,GPIO_ModeDefaultEXTI
PB4.GPIO_Label=LTS
PB4.GPIO_ModeDefaultEXTI=GPIO_MODE_IT_RISING_FALLING
PB4.Signal=GPXTI4
PB5.GPIOParameters=GPIO_Label,GPIO_ModeDefaultEXTI
PB5.GPIO_Label=RTS
PB5.GPIO_ModeDefaultEXTI=GPIO_MODE_IT_RISING_FALLING
PB5.Signal=GPXTI5
PB6.Mode=I2C
PB6.Signal=I2C1_SCL
PB7.Mode=I2C
PB7.Signal=I2C1_SDA
PB8.Mode=TX_Only_Simplex_Unidirect_Master
PB8.Signal=SPI5_MOSI
PB9.GPIOParameters=GPIO_Label,GPIO_ModeDefaultEXTI
PB9.GPIO_Label=REV
PB9.GPIO_ModeDefaultEXTI=GPIO_MODE_IT_RISING_FALLING
PB9.Signal=GPXTI9
PC0.GPIOParameters=PinState,GPIO_PuPd,GPIO_Label
PC0.GPIO_Label=ULED1
PC0.GPIO_PuPd=GPIO_NOPULL
PC0.PinState=GPIO_PIN_SET
PC0.Signal=GPIO_Output
PC1.GPIOParameters=PinState,GPIO_PuPd,GPIO_Label,GPIO_ModeDefaultOutputPP
PC1.GPIO_Label=ULED2
PC1.GPIO_ModeDefaultOutputPP=GPIO_MODE_OUTPUT_PP
PC1.GPIO_PuPd=GPIO_NOPULL
PC1.PinState=GPIO_PIN_SET
PC1.Signal=GPIO_Output
PC10.GPIOParameters=GPIO_Label,GPIO_ModeDefaultEXTI
PC10.GPIO_Label=BRK
PC10.GPIO_ModeDefaultEXTI=GPIO_MODE_IT_RISING_FALLING
PC10.Signal=GPXTI10
PC11.Mode=SD_4_bits_Wide_bus
PC11.Signal=SDIO_D3
PC12.Mode=TX_Only_Simplex_Unidirect_Master
PC12.Signal=SPI3_MOSI
PC3.Mode=TX_Only_Simplex_Unidirect_Master
PC3.Signal=SPI2_MOSI
PC4.GPIOParameters=GPIO_Label
PC4.GPIO_Label=US2
PC4.Signal=GPIO_Input
PC6.Mode=Asynchronous
PC6.Signal=USART6_TX
PC7.Mode=Asynchronous
PC7.Signal=USART6_RX
PC8.Mode=SD_4_bits_Wide_bus
PC8.Signal=SDIO_D0
PC9.Mode=SD_4_bits_Wide_bus
PC9.Signal=SDIO_D1
PD2.Mode=SD_4_bits_Wide_bus
PD2.Signal=SDIO_CMD
PH0\ -\ OSC_IN.Mode=HSE-External-Oscillator
PH0\ -\ OSC_IN.Signal=RCC_OSC_IN
PH1\ -\ OSC_OUT.Mode=HSE-External-Oscillator
PH1\ -\ OSC_OUT.Signal=RCC_OSC_OUT
RCC.HSE_VALUE=16000000
RCC.SYSCLKFreq_VALUE=96000000
RCC.SYSCLKSource=RCC_SYSCLKSOURCE_PLLCLK

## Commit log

2018-04-12 Add files via upload
    Initial addition of onboard sensor libraries and "AES_Final_Config" STM32Cube project file used to generate peripheral initialization / skeleton code
2018-04-12 Rename FXAS21002C/FXAS21002C.c to Software/FXAS21002C/FXAS21002C.c
2018-04-12 Rename FXAS21002C/FXAS21002C.h to Software/FXAS21002C/FXAS21002C.h
2018-04-12 Rename LIS3MDL/LIS3MDL.c to Software/LIS3MDL/LIS3MDL.c
2018-04-12 Rename LIS3MDL/LIS3MDL.h to Software/LIS3MDL/LIS3MDL.h
2018-04-12 Rename AES_Final_Config/AES_Final_Config.ioc to Software/PeripheralConfigurationCube/AES_Final_Config.ioc
2018-04-12 Rename LIS3DH/LIS3DH.c to Software/LIS3DH/LIS3DH.c
2018-04-12 Rename LIS3DH/LIS3DH.h to Software/LIS3DH/LIS3DH.h
2018-04-12 Rename Software/LIS3MDL/LIS3MDL.h to Software/Libraries/OnboardSensors/LIS3MDL.h
2018-04-12 Rename Software/LIS3MDL/LIS3MDL.c to Software/Libraries/OnboardSensors/LIS3MDL/LIS3MDL.c
2018-04-12 Rename Software/Libraries/OnboardSensors/LIS3MDL.h to Software/Libraries/OnboardSensors/LIS3MDL/LIS3MDL.h
2018-04-12 Rename Software/LIS3DH/LIS3DH.c to Software/Libraries/LIS3D/LIS3DH.c
2018-04-12 Rename Software/Libraries/LIS3D/LIS3DH.c to Software/Libraries/OnboardSensors/LIS3DH/LIS3DH.c
2018-04-12 Rename Software/LIS3DH/LIS3DH.h to Software/Libraries/OnboardSensors/LIS3DH/LIS3DH.h
2018-04-12 Rename Software/FXAS21002C/FXAS21002C.c to Software/Libraries/OnboardSensors/FXAS21002C/FXAS21002C.c
2018-04-12 Rename Software/FXAS21002C/FXAS21002C.h to Software/Libraries/OnboardSensors/FXAS21002C/FXAS21002C.h
2018-04-12 Rename SeeedSpecs/SeeedStudio_2layer_DRU_no_angle_20140221.dru to Hardware/EagleFiles/SeeedSpecs/SeeedStudio_2layer_DRU_no_angle_20140221.dru
2018-04-12 Rename SeeedSpecs/SeeedStudio_4layer_DRU_no_angle_20140221.dru to Hardware/EagleFiles/SeeedSpecs/SeeedStudio_4layer_DRU_no_angle_20140221.dru
2018-04-12 Rename SeeedSpecs/Seeed_Gerber_Generater_2-layer.cam to Hardware/EagleFiles/SeeedSpecs/Seeed_Gerber_Generater_2-layer.cam
2018-04-12 Rename SeeedSpecs/Seeed_Gerber_Generater_4-layer_1-2-15-16.cam to Hardware/EagleFiles/SeeedSpec/Seeed_Gerber_Generater_4-layer_1-2-15-16.cam
2018-04-12 Rename Hardware/EagleFiles/SeeedSpec/Seeed_Gerber_Generater_4-layer_1-2-15-16.cam to Hardware/EagleFiles/SeeedSpecs/Seeed_Gerber_Generater_4-layer_1-2-15-16.cam
2018-04-12 Rename AES_HWR1_M2018.brd to Hardware/EagleFiles/Board/AES_HWR1_M2018.brd
2018-04-12 Rename AES_HWR1_M2018.sch to Hardware/EagleFiles/Boards/AES_HWR1_M2018.sch
2018-04-12 Rename Hardware/EagleFiles/Boards/AES_HWR1_M2018.sch to Hardware/EagleFiles/Board/AES_HWR1_M2018.sch
2018-05-02 Rename Software/LidarLiteV3/LIDARLITEV3.c to Software/Libraries/LidarLiteV3/LIDARLITEV3.c
2018-05-02 Rename Software/LidarLiteV3/LIDARLITEV3.h to Software/Libraries/LidarLiteV3/LIDARLITEV3.h
2018-05-02 Rename Software/STN2120/STN2120.c to Software/Libraries/STN2120/STN2120.c
2018-05-02 Rename Software/STN2120/STN2120.h to Software/Libraries/STN2120/STN2120.h
2018-05-02 Rename Software/Serial/serial.c to Software/Libraries/Serial/serial.c
2018-05-02 Rename Software/Serial/serial.h to Software/Libraries/Serial/serial.h
2018-05-03 Add demos
    These demos are compressed Atollic TrueSUDIO projects. They contain all necessary source code independently.

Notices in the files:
Hardware/EagleFiles/Board/AES_HWR1_M2018.brd:
© Owen Lyke, March 2018
